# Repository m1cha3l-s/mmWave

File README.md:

# mmWave playKit
mmwave sensing project using seeedstudio 24GHz mmwave sensor and xiao esp32-s3

### Firmware notice
The included firmware is not fine tuned as of now because this project isn't built in real life as of yet. Also the included firmware is for controlling a different project of mine [Remote Occupancy Indicator](https://github.com/m1cha3l-s/remote-occupancy-indicator). The idea behind this project is to explore what's possible with this and try it in real world conditions so that you can have a better idea in which scenarios this sensor is usefull and in which it would lack functionality, with this idea comes the need of your own firmware to use it in your situation!

### Case notice
As of right now I don't have the parts on hand so I can't make the case. Without the sizes making a case at this point in making would be pointless. I have done my research tho and I know the headers and everything should be possible to fit. If I am mistaken then I take it as my mistake and will redo and order the stuff myself if needed.

## Building
1. Solder the headers included with the module together with the PCB and ESP32. (Make sure the headers are on the sides with the silkscreen text)
2. Solder the headers from the ESP32 onto the module.
3. Solder the LEDs onto the PCB.
4. Connect the module to the headers on the PCB.
5. Place it inside the optional 3D Printed case.
6. Now you are finished!!!

#### This is how it should be looking together

## Flashing (Sensor for [Remote Occupancy Indicator](https://github.com/m1cha3l-s/remote-occupancy-indicator))
1. Flash the MAC-Finder in Arduino IDE (It can be found in the folder with the firmware).
2. Look into the serial monitor and write down the MAC address. (We will need this to be able to communicate with the Indicator.
3. For this demo to work we will need to reflash the Indicator with the MAC of the sensor.
4. After doing that flash the sensor with the MAC of the indicator.
5. Now you are finished!!! The sensor and indicator will connect automatically.

## PCB/Schematic

### BOM
| Part Name | Quantity | Price (USD) | Total (USD) | Link |
|---|---|---|---|---|
| XIAO ESP32-S3 | 1 | 10 | 10 | https://botland.cz/moduly-wifi-a-bt-esp32/22878-seeed-xiao-esp32-s3-wifi-bluetooth-seeedstudio-113991114.html |
| 24Ghz mmwave seeedstudio sensor | 1 | 6.70 | 6.70 | https://botland.cz/pohybove-senzory/24129-human-static-presence-mmwave-24ghz-senzor-pro-seeed-xiao-seeedstudio-101010001.html |
| botland shipping | 1 | 3.60 | 3.60 | |
| Custom PCB (with shipping) | 1 | 4.36 | 4.36 | jlcpcb |
| 3D Printed case | 1 | 0 | 0 | none - I have my own printer |
| Total ||| 24.66 |

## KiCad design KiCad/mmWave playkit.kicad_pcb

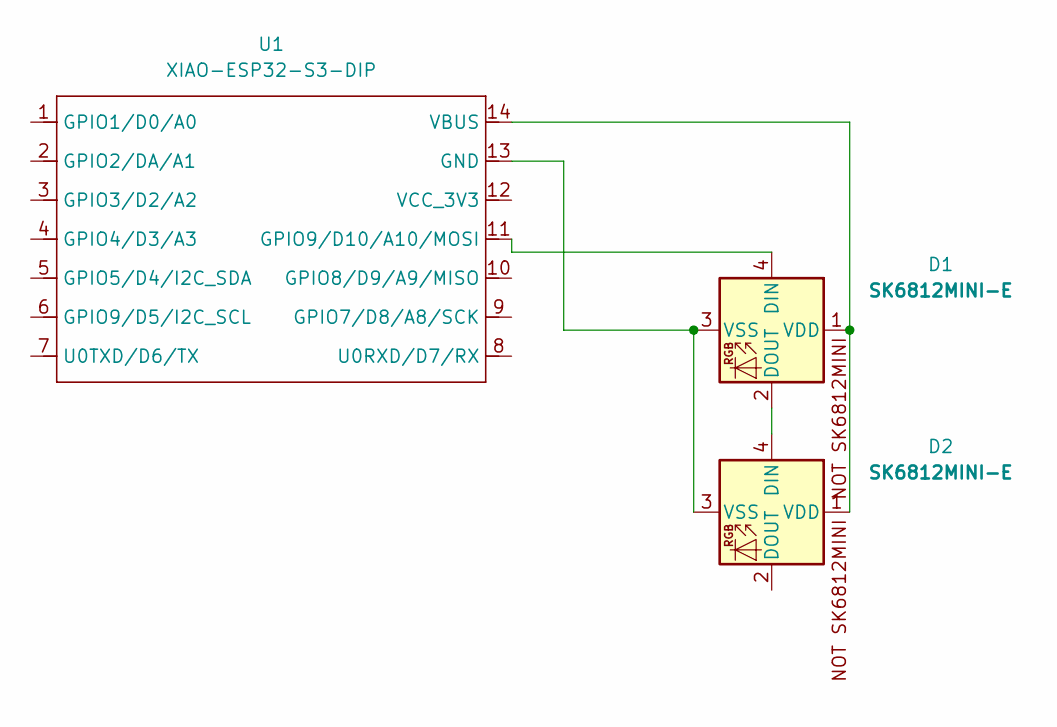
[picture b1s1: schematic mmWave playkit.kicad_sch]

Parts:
D1, D2: SK6812MINI-E; SK6812MINI-E_fixed
U1: XIAO-ESP32-S3-DIP; XIAO-ESP32S3-DIP

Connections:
unnamed: D1.4 (DIN), U1.11 (GPIO9/D10/A10/MOSI)
unnamed: D1.2 (DOUT), D2.4 (DIN)
unnamed: D1.1 (VDD), D2.1 (VDD), U1.14 (VBUS)
unnamed: D1.3 (VSS), D2.3 (VSS), U1.13 (GND)

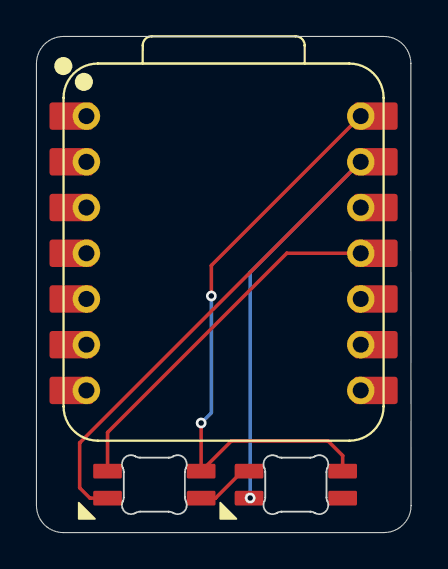
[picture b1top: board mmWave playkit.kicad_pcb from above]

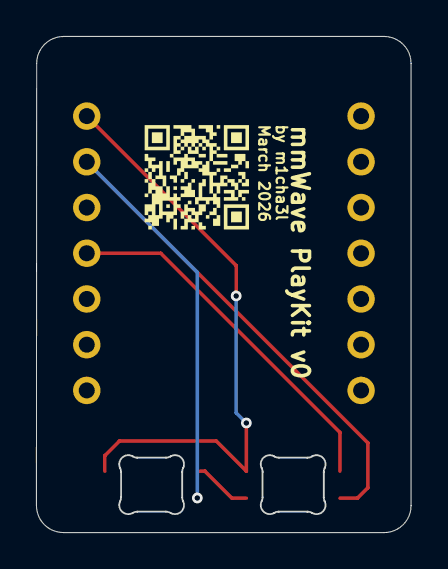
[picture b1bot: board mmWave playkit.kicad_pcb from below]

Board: 2 copper layers, 20.8 x 27.5 mm, 4 parts (3 on the bottom side), 4 nets.

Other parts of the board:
QR*****: github.com/m1cha3l-s; github-qr

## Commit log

2026-03-23 added BOM
2026-03-24 added kicad files
2026-03-24 added pics
2026-03-30 Added pcb 3d model
